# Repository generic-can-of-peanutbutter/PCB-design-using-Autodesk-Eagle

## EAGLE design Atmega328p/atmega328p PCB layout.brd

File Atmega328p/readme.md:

This project contains a custom PCB layout for the ATmega328P microcontroller, along with supporting components such as voltage regulation, LEDs, connectors, and I/O ports. The design is created in Autodesk EAGLE and intended as a general-purpose microcontroller development board.

The board includes:

ATmega328P (DIP-28 package)

7805 voltage regulator

Input power connector

LEDs and resistors

External pin headers for I/O

Supporting discrete components and connectors

🖼️ PCB Layout Preview

(This section corresponds to the PCB image you shared)
The layout includes:

Regulator section on top

ATmega328P in the center

Multiple connectors on left/right

LED indicators

Routing for all microcontroller pins

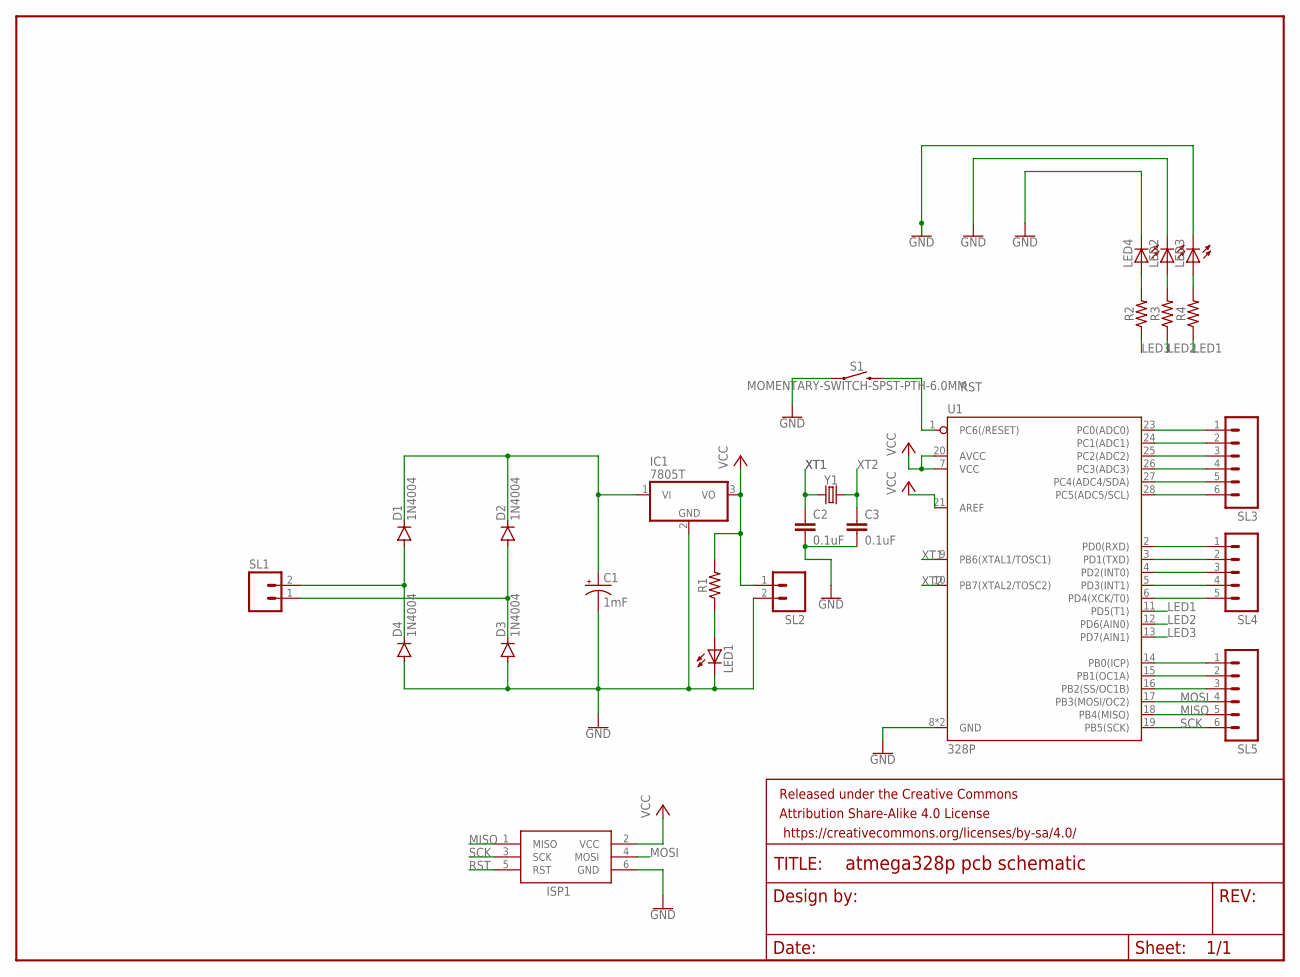
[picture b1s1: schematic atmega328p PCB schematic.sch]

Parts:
C1: 1mF; CPOL-RADIAL-5MM-10MM
C2, C3: 0.1uF; CAP-PTH-SMALL-KIT
D1, D2, D3, D4: 1N4004; DO41-10
FRAME1: FRAME-LETTERNO_PACKAGE; DUMMY
IC1: 7805T; TO220H
ISP1: AVRISP-6; AVRISP
LED1: LED5MM
LED2, LED3, LED4: LED3MM
R1, R2, R3, R4: AXIAL-0.3
S1: MOMENTARY-SWITCH-SPST-PTH-6.0MM; TACTILE_SWITCH_PTH_6.0MM
SL1, SL2: M02; 02P
SL3, SL5: M06; 06P
SL4: M05; 05P
U1: 328P; DIP28
Y1: CRYSTALPTH-HC49US; HC49US

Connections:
GND: C1.-, C2.2, C3.2, D3.A, D4.A, IC1.2 (GND), ISP1.6 (GND), LED1.K (C), LED2.K (C), LED3.K (C), LED4.K (C), S1.1, SL2.2, U1.8 (GND), U1.22 (GND)
LED1: R4.P$1 (1), U1.11 (PD5(T1))
LED2: R3.P$1 (1), U1.12 (PD6(AIN0))
LED3: R2.P$1 (1), U1.13 (PD7(AIN1))
MISO: ISP1.1 (MISO), SL5.5, U1.18 (PB4(MISO))
MOSI: ISP1.4 (MOSI), SL5.4, U1.17 (PB3(MOSI/OC2))
unnamed: C1.+, D1.C, D2.C, IC1.1 (VI)
unnamed: D1.A, D4.C, SL1.2
unnamed: D2.A, D3.C, SL1.1
unnamed: SL3.1, U1.23 (PC0(ADC0))
unnamed: LED1.A, R1.P$1 (1)
unnamed: LED4.A, R2.P$2 (2)
unnamed: LED2.A, R3.P$2 (2)
unnamed: LED3.A, R4.P$2 (2)
unnamed: SL3.2, U1.24 (PC1(ADC1))
unnamed: SL3.3, U1.25 (PC2(ADC2))
unnamed: SL3.4, U1.26 (PC3(ADC3))
unnamed: SL3.5, U1.27 (PC4(ADC4/SDA))
unnamed: SL3.6, U1.28 (PC5(ADC5/SCL))
unnamed: SL4.1, U1.2 (PD0(RXD))
unnamed: SL4.2, U1.3 (PD1(TXD))
unnamed: SL4.3, U1.4 (PD2(INT0))
unnamed: SL4.4, U1.5 (PD3(INT1))
unnamed: SL4.5, U1.6 (PD4(XCK/T0))
unnamed: SL5.1, U1.14 (PB0(ICP))
unnamed: SL5.2, U1.15 (PB1(OC1A))
unnamed: SL5.3, U1.16 (PB2(SS/OC1B))
RST: ISP1.5 (RST), S1.3 (2), U1.1 (PC6(/RESET))
SCK: ISP1.3 (SCK), SL5.6, U1.19 (PB5(SCK))
VCC: IC1.3 (VO), ISP1.2 (VCC), R1.P$2 (2), SL2.1, U1.7 (VCC), U1.20 (AVCC), U1.21 (AREF)
XT1: C2.1, U1.9 (PB6(XTAL1/TOSC1)), Y1.1
XT2: C3.1, U1.10 (PB7(XTAL2/TOSC2)), Y1.2

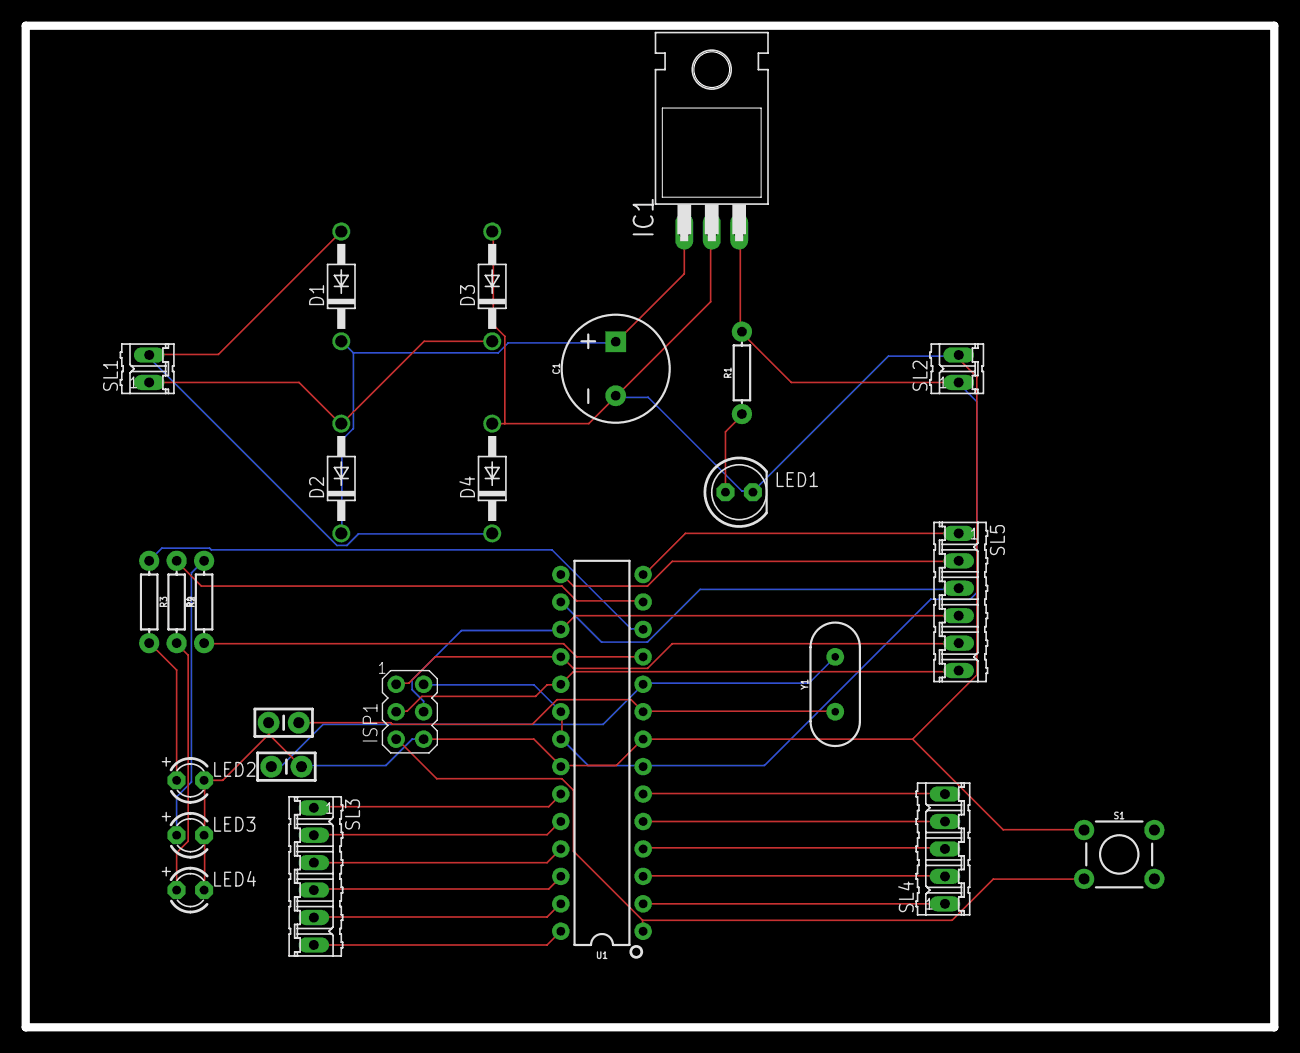
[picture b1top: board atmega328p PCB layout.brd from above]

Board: 2 copper layers, 115.6 x 92.7 mm, 26 parts (0 on the bottom side), 32 nets.

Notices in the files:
parts and their libraries:
SparkFun-Capacitors: Licensing: Creative Commons ShareAlike 4.0 International - https://creativecommons.org/licenses/by-sa/4.0
SparkFun-Aesthetics: Released under the Creative Commons Attribution Share-Alike 4.0 License
SparkFun-Aesthetics: https://creativecommons.org/licenses/by-sa/4.0
